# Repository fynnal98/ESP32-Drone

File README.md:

# ESP32-Drone
## Project Images

---
## Software
The code is structurd in modules:

**main**  
- Init: SBUS, IMU, PWM, LED, Battery  
- Safety: Failsafe, Low-voltage, Arming  
- Motor mix: Inputs + PID corrections  
**SbusReceiver**  
- Reads SBUS signal  
- Maps + filters channels  
- Deadband, scaling, failsafe check  

**MPU6050**  
- Reads gyro + accel  
- Complementary filter for roll/pitch  
- Provides orientation data  

**PidController**  
- Generic PID loop  
- Used for roll and pitch stabilization  (no yaw!)

**FlightController**  
- Reads roll/pitch targets from SBUS and actual values from IMU  
- Runs PID controllers for roll and pitch  
- Outputs correction values (but the Donelogic is used in main yet.)

**config.h**  
- Pin definitions  
- PID parameters  
- PWM setup  
- Battery thresholds 

---
## Hardware

Hardware:  
- ESP32-C3  
- MPU6050 // MPU6500  
- SBUS Receiver (serial data from RadioLink remote controller)  
- 4 × Brushed DC Motors (3.7 V)  
- Custom Motor Drivers (MOSFET + gate resistor + pull-down + Schottky diode)  
- 1S LiPo Battery  
- Resistor Divider (for battery voltage measurement)  
- LED Indicator (low-voltage warning)  
- Capacitors for voltage spikes  

The system is based on an ESP32-C3 Super Mini microcontroller combined with an MPU6500 IMU for orientation sensing.  
Remote control signals are received by a serial SBUS input.  
Four DC brushed motors are controlled by custom motor drivers. Each is build with a Mosfet, pulldown resisitor and a shottky diode.

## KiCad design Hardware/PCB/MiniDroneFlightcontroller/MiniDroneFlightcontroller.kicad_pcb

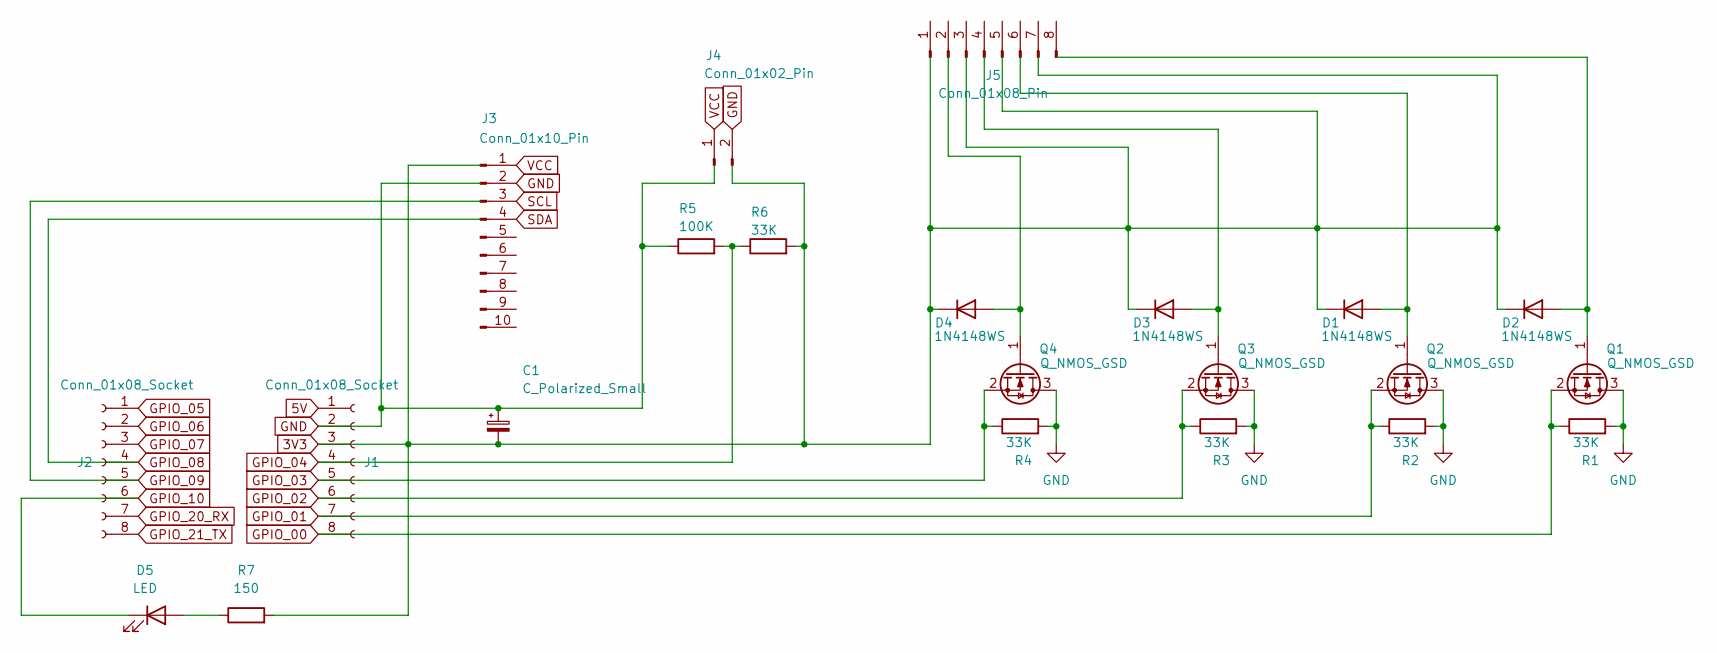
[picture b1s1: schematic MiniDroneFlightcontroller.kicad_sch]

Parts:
C1: C_Polarized_Small; CP_Radial_D8.0mm_P5.00mm
D1, D2, D3, D4: 1N4148WS; D_SOD-323
D5: LED; LED_D4.0mm
J1, J2: Conn_01x08_Socket; PinSocket_1x08_P2.54mm_Vertical
J3: Conn_01x10_Pin; PinHeader_1x10_P2.54mm_Vertical
J4: Conn_01x02_Pin; PinHeader_1x02_P2.54mm_Vertical
J5: Conn_01x08_Pin; PinHeader_1x08_P2.54mm_Vertical
Q1, Q2, Q3, Q4: Q_NMOS_GSD; SOT-23
R1, R2, R3, R4, R6: 33K; R_0805_2012Metric
R5: 100K; R_0805_2012Metric
R7: 150; R_0805_2012Metric

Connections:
3V3: C1.2, D1.1 (K), D2.1 (K), D3.1 (K), D4.1 (K), J1.3, R6.2, R7.2
5V: J1.1
GND: C1.1, J1.2, J3.2, J4.2, Q1.3 (D), Q2.3 (D), Q3.3 (D), Q4.3 (D), R1.2, R2.2, R3.2, R4.2, R5.1
GPIO_00: J1.8, Q1.2 (S), R1.1
GPIO_01: J1.7, Q2.2 (S), R2.1
GPIO_02: J1.6, Q3.2 (S), R3.1
GPIO_03: J1.5, Q4.2 (S), R4.1
GPIO_04: J1.4, R5.2, R6.1
GPIO_05: J2.1
GPIO_06: J2.2
GPIO_07: J2.3
GPIO_08: J2.4
GPIO_09: J2.5
GPIO_10: D5.1 (K), J2.6
GPIO_20_RX: J2.7
GPIO_21_TX: J2.8
unnamed: D1.2 (A), Q2.1 (G)
unnamed: D2.2 (A), Q1.1 (G)
unnamed: D3.2 (A), Q3.1 (G)
unnamed: D4.2 (A), Q4.1 (G)
unnamed: D5.2 (A), R7.1
SCL: J3.3
SDA: J3.4
VCC: J3.1, J4.1

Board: 2 copper layers, 22 parts (0 on the bottom side), 14 nets, no tracks yet.

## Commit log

2025-08-28 merge
2026-02-21 change to esp32c
2026-02-21 low filter
2026-02-22 asdihj
2026-02-22 NEW SW
2026-02-22 stable version
